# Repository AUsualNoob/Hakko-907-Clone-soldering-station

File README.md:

# Hakko 907 Soldering Station

## Features

- Arduino Nano based control
- Compatible with Hakko 907 / 907C style handles
- Temperature monitoring
- Adjustable temperature control

---

## PCB

### Schematic

Took me a long while. Research and part searching is hard man.

### Tracing

I had to make it 4 layer for my sake, I wouldn't be able to make it 2 layer.

---

## Firmware

There are 2 versions of the firmware.

### Bang-Bang (BB)

Works by having the transistor at either max PWM value or 0 PWM value for increasing and decreasing temperature.

### PID (Proportional-Integral-Derivative)

Adjusts the PWM value depending on how far the current temperature is from the wanted temperature.

It all starts with an error value.

#### Error

The error value is calculated by subtracting the wanted temperature by the current temperature.

```
Error = wantedTemp - currentTemp
```

#### Proportional

That error value is multiplied by a `kP` value. The `kP` value is tweaked to ensure it works properly, it has a default of `2`. The product of the error value and the `kP` value is going to be a part of the PWM value.

```
PWM = kP * Error
```

#### Integral

The integral value has a default of `0`. Usually if the error value gets smaller, the less power goes into the iron, so it usually stays at 10–20 degrees celsius less than the wanted value. This is where the integral comes in — it keeps getting added so you can reach the temperature. It's then multiplied by `kI`, which is also something that should be tweaked, it has a default of `0.5`.

```
integral = integral + error
```

#### Derivative

However the integral value and the error value together usually overshoots, and that's where the derivative comes in. It's then multiplied by `kD`, which has a default value of `0.1` and should also be tweaked.

```
derivative = error - lastError
```

#### Final Output

In the end, it's all put into one float variable, called `pid`, which is then constrained to then be an integer pwm value.

```
pid = (kP * Error) + (kI * integral) + (kD * derivative)
```

```cpp
int pwm = constrain((int)pid, 0, 255);
```

---

## CAD

Fusion is hard man.

---

## Finished Product

### Outside

### Inside

---

## BOM

| Qty | Part | Purpose | Cost (USD) | Distributor |
|-----|------|---------|------------|-------------|
| 2x | [5mm LEDS](https://www.ram-e-shop.com/shop/led-gg-led-5mm-green-color-5940) | Knowing when it's on or off | 0.019$ | Ram Electronics |
| 1x | [Arduino Nano v3.x](https://www.ram-e-shop.com/shop/kit-arduino-nano-ch340-arduino-nano-328-with-ch340-chip-clone-8338) | Brain of the device | $5.00 | Ram Electronics |
| 1x | [1000µF 50V capacitor](https://www.ram-e-shop.com/shop/c-1000u50v-capacitor-1000uf-50v-6104) | Passive component | $0.10 | Ram Electronics |
| 1x | [100µF 50V capacitor](https://www.ram-e-shop.com/shop/c-100u50v-capacitor-100uf-50v-6073) | Passive component | $0.03 | Ram Electronics |
| 1x | [1N5822](https://www.amazon.eg/-/en/5pcs-1N5822-5822-1N582-Diode/dp/B0DWY2S9S8) | Passive component | $3.00 | Amazon |
| 1x | [1.3" 128x64 I2C OLED display](https://www.ram-e-shop.com/shop/oled-1-3-4pin-oled-1-3-4pin-lcd-display-module-i2c-iic-communicate-7794) | Displaying temperature | $1.75 | Ram Electronics |
| 1x | [1N5240B zener diode](https://www.amazon.eg/-/en/gp/product/B0CWPCPZN2) | Zener diode | $1.50 | Amazon |
| 1x | [RUEF300 polyfuse](https://www.amazon.eg/-/en/gp/product/B0FNLD9RPG) | Protection passive component | $2.00 | Amazon |
| 1x | [GX16-5 connector](https://www.ram-e-shop.com/shop/gx16-5pin-gx16-5-pole-metal-male-female-panel-chassis-connector-7025) | Connector for soldering iron | $1.00 | Ram Electronics |
| 1x | [DC barrel jack](https://www.amazon.eg/-/en/gp/product/B0D4N6JF7F) | Input plug for power | $1.00 | Amazon |
| 1x | [100µH inductor](https://www.amazon.eg/-/en/gp/product/B0FF9X6THF) | Noise reduction | $1.50 | Amazon |
| 1x | [IRF4905 MOSFET](https://www.amazon.eg/-/en/IRF4905-P-Channel-HEXFET-MOSFET-74A/dp/B09H13NQD4) | P-channel MOSFET for reverse polarity protection | $2.00 | Amazon |
| 1x | [IRLZ44N MOSFET](https://www.ram-e-shop.com/shop/irlz44-irlz44n-logic-level-gate-n-channel-mosfet-6633) | N-channel MOSFET for heater control | $1.00 | Ram Electronics |
| 1x | [100k resistor](https://www.ram-e-shop.com/shop/carbon-resistance-1-4w-price-per-4-resistors-9506#attr=314) | Passive component | $0.40 | Ram Electronics |
| 1x | [10k resistor](https://www.ram-e-shop.com/shop/carbon-resistance-1-4w-price-per-4-resistors-9506#attr=314) | Passive component | $0.02 | Ram Electronics |
| 1x | [470Ω resistor](https://www.ram-e-shop.com/shop/carbon-resistance-1-4w-price-per-4-resistors-9506#attr=307) | Passive component | $0.02 | Ram Electronics |
| 1x | [3.3k resistor](https://www.amazon.eg/-/en/Resistor-Through-Electronics-Circuit-Projects/dp/B0GYQ2GYK1) | Passive component | $1.50 | Amazon |
| 1x | [2.7k resistor](https://www.ram-e-shop.com/shop/carbon-resistance-1-4w-price-per-4-resistors-9506#attr=307) | Passive component | $0.02 | Ram Electronics |
| 2x | [2.2k resistor](https://www.amazon.eg/-/en/Resistor-Through-Electronics-Circuit-Projects/dp/B0GYQ2GYK1) | Passive component | $1.00 | Amazon |
| 1x | [Rotary encoder](https://www.ram-e-shop.com/shop/pot-ec11-rotary-5pin-20mm-ec11-rotary-encoder-with-push-button-switch-5pin-20mm-silver-9624) | Controlling temperature | $0.50 | Ram Electronics |
| 1x | [LM2576](https://www.amazon.eg/-/en/gp/product/B0FHHC669J) | Step down converter for the Arduino | $2.00 | Amazon |
| 1x | [LM358 op-amp](https://www.ram-e-shop.com/shop/lm358-copy-lm358p-copy-6130) | OPAMP for amplifying | $0.10 | Ram Electronics |
| 1x | [Soldering Iron Handle](https://www.amazon.eg/-/en/Home-Soldering-Desoldering-Solder-Station/dp/B0GCSY3SBH/ref=sr_1_7?crid=164RY93DEOGSH&dib=eyJ2IjoiMSJ9.oCii5B0EJOsOawhvu71j2wZhxK530PdLNBRV6zdfw3OTkg1bqy9Yza85gD998wNN5HrHseDyYSVGOqD3hhtNVk6EGwazw0Ifr6qm7G5Nc9aeKXNLEXccIUOAhkQdMeVWgLRELA1Q0lunMn9dBY4rNqdgxpqJ6kCvdFOx1OawHm3lGXM1f2BZOPYWBCD0mLDAcphNL7xB0_6o7BtSDkXERMccpYQZjLgv-jea5Jj_LPzZnS8gFeBS01P8wHm20pf7cbIObiJ8NbOkE0pC-3s5_JlGeBRfxMo3UMOcEvQLn_c.uLxslEId-HzDGxANhADrrzYBeEtk4ObHqa4aIK8KpVg&dib_tag=se&keywords=soldering+iron+handle&qid=1778771214&sprefix=soldering+iron+handl%2Caps%2C188&sr=8-7) | The handle for the device | 8.20$ | Amazon |
| 1x | [DC Power Adaptor](https://www.amazon.eg/-/en/gp/product/B0FXBHBNHM/ref=ewc_pr_img_7?smid=A2DMKAT7ZKLGQN&psc=1) | Powering the device | 12.41$ | Amazon |
| 5x | PCB | Electrical connections and main body | 7$ | JLCPCB |

**Subtotal: ~$53.1**

**Shipping and Tax: 30$**

**Total: ~83.1$**

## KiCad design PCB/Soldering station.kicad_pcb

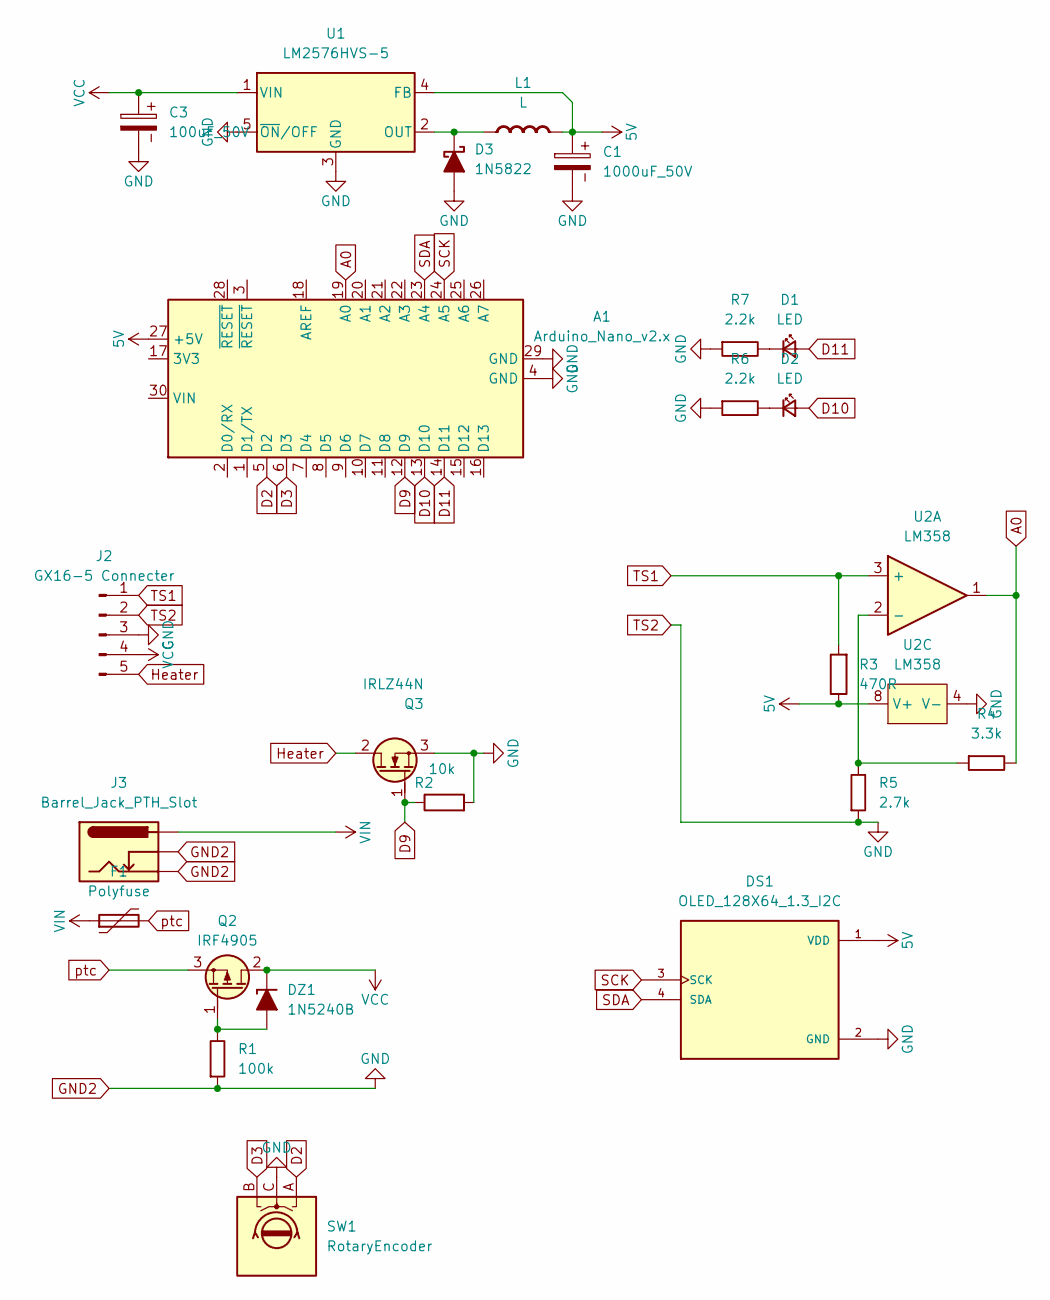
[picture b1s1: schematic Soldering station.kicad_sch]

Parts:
A1: Arduino_Nano_v2.x; Arduino_Nano
C1: 1000uF_50V; CP_Radial_D8.0mm_P2.50mm
C3: 100uF_50V; CP_Radial_D8.0mm_P3.50mm
D1, D2: LED; LED_D5.0mm
D3: 1N5822; D_DO-201AD_P12.70mm_Horizontal
DS1: OLED_128X64_1.3_I2C; LCD_OLED_128X64_1.3_I2C; PARTREV NA
DZ1: 1N5240B; D_DO-35_SOD27_P7.62mm_Horizontal_Zener
F1: Polyfuse; Fuse_BelFuse_0ZRE0005FF_L8.3mm_W3.8mm
J2: GX16-5 Connecter; GX16-5
J3: Barrel_Jack_PTH_Slot
L1: L; L_Toroid_Horizontal_D3.2mm_P6.40mm_Diameter3-5mm_Amidon-T12; Rating A
Q2: IRF4905; TO-220-3_Horizontal_TabDown
Q3: IRLZ44N; TO-220-3_Horizontal_TabDown
R1: 100k; R_Axial_DIN0207_L6.3mm_D2.5mm_P10.16mm_Horizontal
R2: 10k_0402; R_Axial_DIN0207_L6.3mm_D2.5mm_P10.16mm_Horizontal; Part Number RT0402FRE0710KL
R3: 470R_0603; R_Axial_DIN0207_L6.3mm_D2.5mm_P10.16mm_Horizontal; Part Number RC0603FR-07470RL; JLCPCB ID C23179
R4: 3.3k; R_Axial_DIN0207_L6.3mm_D2.5mm_P10.16mm_Horizontal
R5: 2.7k; R_Axial_DIN0207_L6.3mm_D2.5mm_P10.16mm_Horizontal
R6, R7: 2.2k; R_Axial_DIN0207_L6.3mm_D2.5mm_P10.16mm_Horizontal
SW1: RotaryEncoder; RotaryEncoder_Alps_EC12E_Vertical_H20mm
U1: LM2576HVS-5; TO-220-5_Horizontal_TabDown
U2: LM358; DIP-8pin_TH; JLCPCB ID C7951

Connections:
5V: A1.27 (+5V), C1.1, DS1.1 (VDD), L1.2 (-), R3.1, U1.4 (FB), U2.8 (V+)
A0: A1.19 (A0), R4.2, U2.1
D2: A1.5 (D2), SW1.A
D3: A1.6 (D3), SW1.B
D9: A1.12 (D9), Q3.1 (G), R2.1
D10: A1.13 (D10), D2.2 (A)
D11: A1.14 (D11), D1.2 (A)
GND2: A1.4 (GND), A1.29 (GND), C1.2, C3.2, D3.2 (A), DS1.2 (GND), J2.2, J2.3, J3.GND, J3.GNDBREAK, Q3.3 (S), R1.1, R2.2, R5.1, R6.1, R7.1, SW1.C, U1.3 (GND), U1.5 (~ON/OFF), U2.4 (V-)
Heater: J2.5, Q3.2 (D)
unnamed: D1.1 (K), R7.2
unnamed: D2.1 (K), R6.2
unnamed: D3.1 (K), L1.1 (+), U1.2 (OUT)
unnamed: DZ1.2 (A), Q2.1 (G), R1.2
unnamed: R4.1, R5.2, U2.2 (-)
SCK: A1.24 (A5), DS1.3 (SCK)
SDA: A1.23 (A4), DS1.4 (SDA)
TS1: J2.1, R3.2, U2.3 (+)
VCC: C3.1, DZ1.1 (K), J2.4, Q2.2 (D), U1.1 (VIN)
VIN: F1.1, J3.PWR
ptc: F1.2, Q2.3 (S)

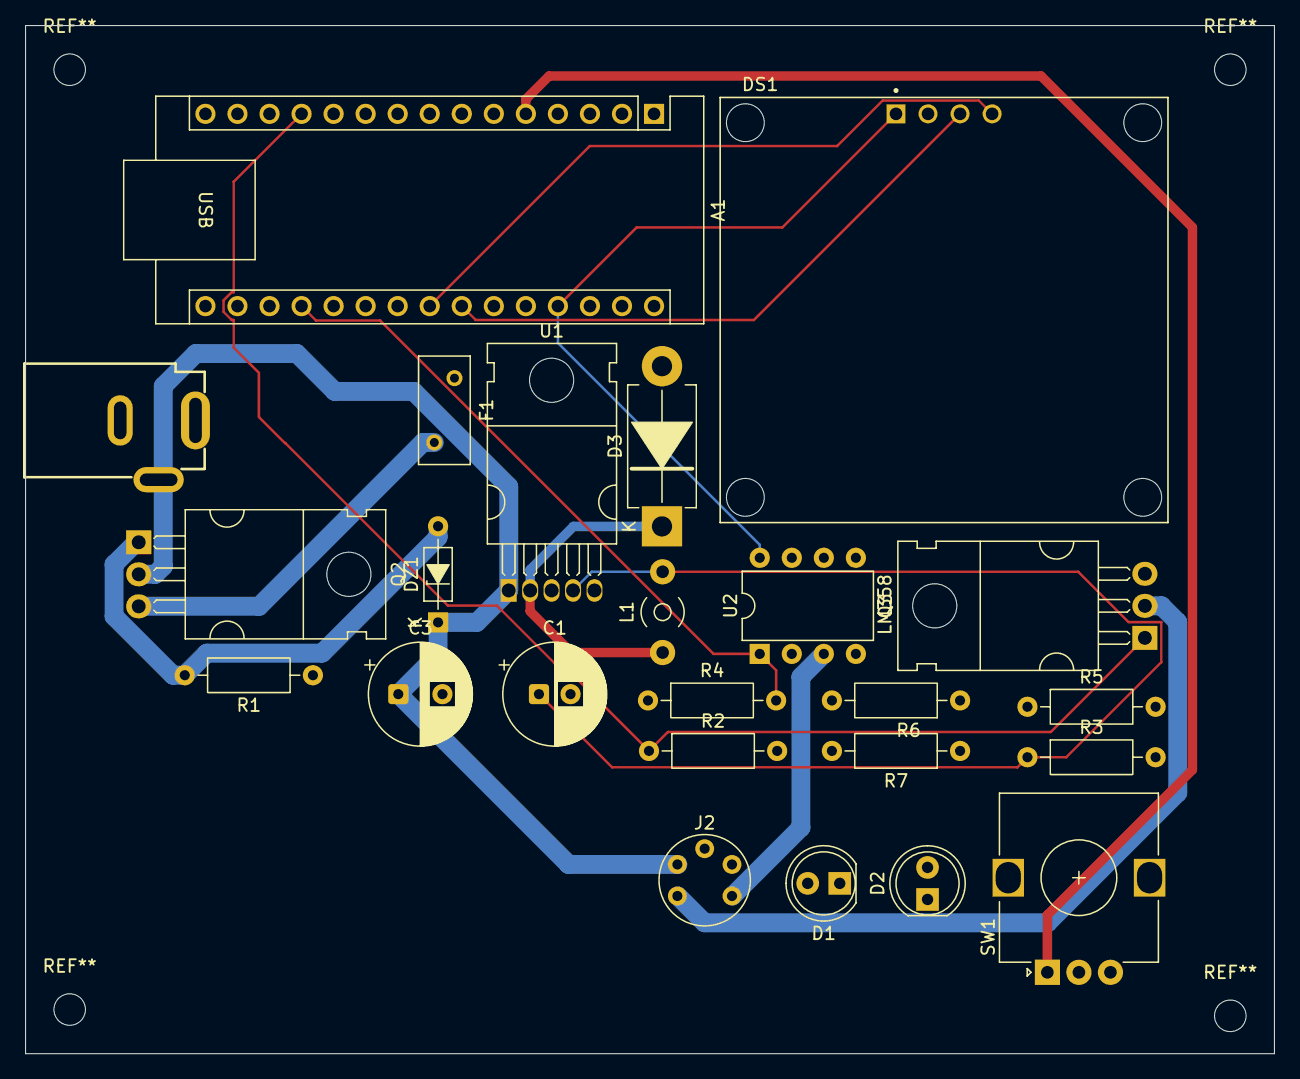
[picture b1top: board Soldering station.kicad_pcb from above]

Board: 4 copper layers, 99.0 x 81.5 mm, 24 parts (0 on the bottom side), 20 nets.
